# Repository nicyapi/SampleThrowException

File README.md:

<<<<<<< Updated upstream
<<<<<<< Updated upstream
# Lighthouse CI
=======
# Senior-Design-Project-maste
 
>>>>>>> Stashed changes
=======
# Senior-Design-Project-maste
 
>>>>>>> Stashed changes

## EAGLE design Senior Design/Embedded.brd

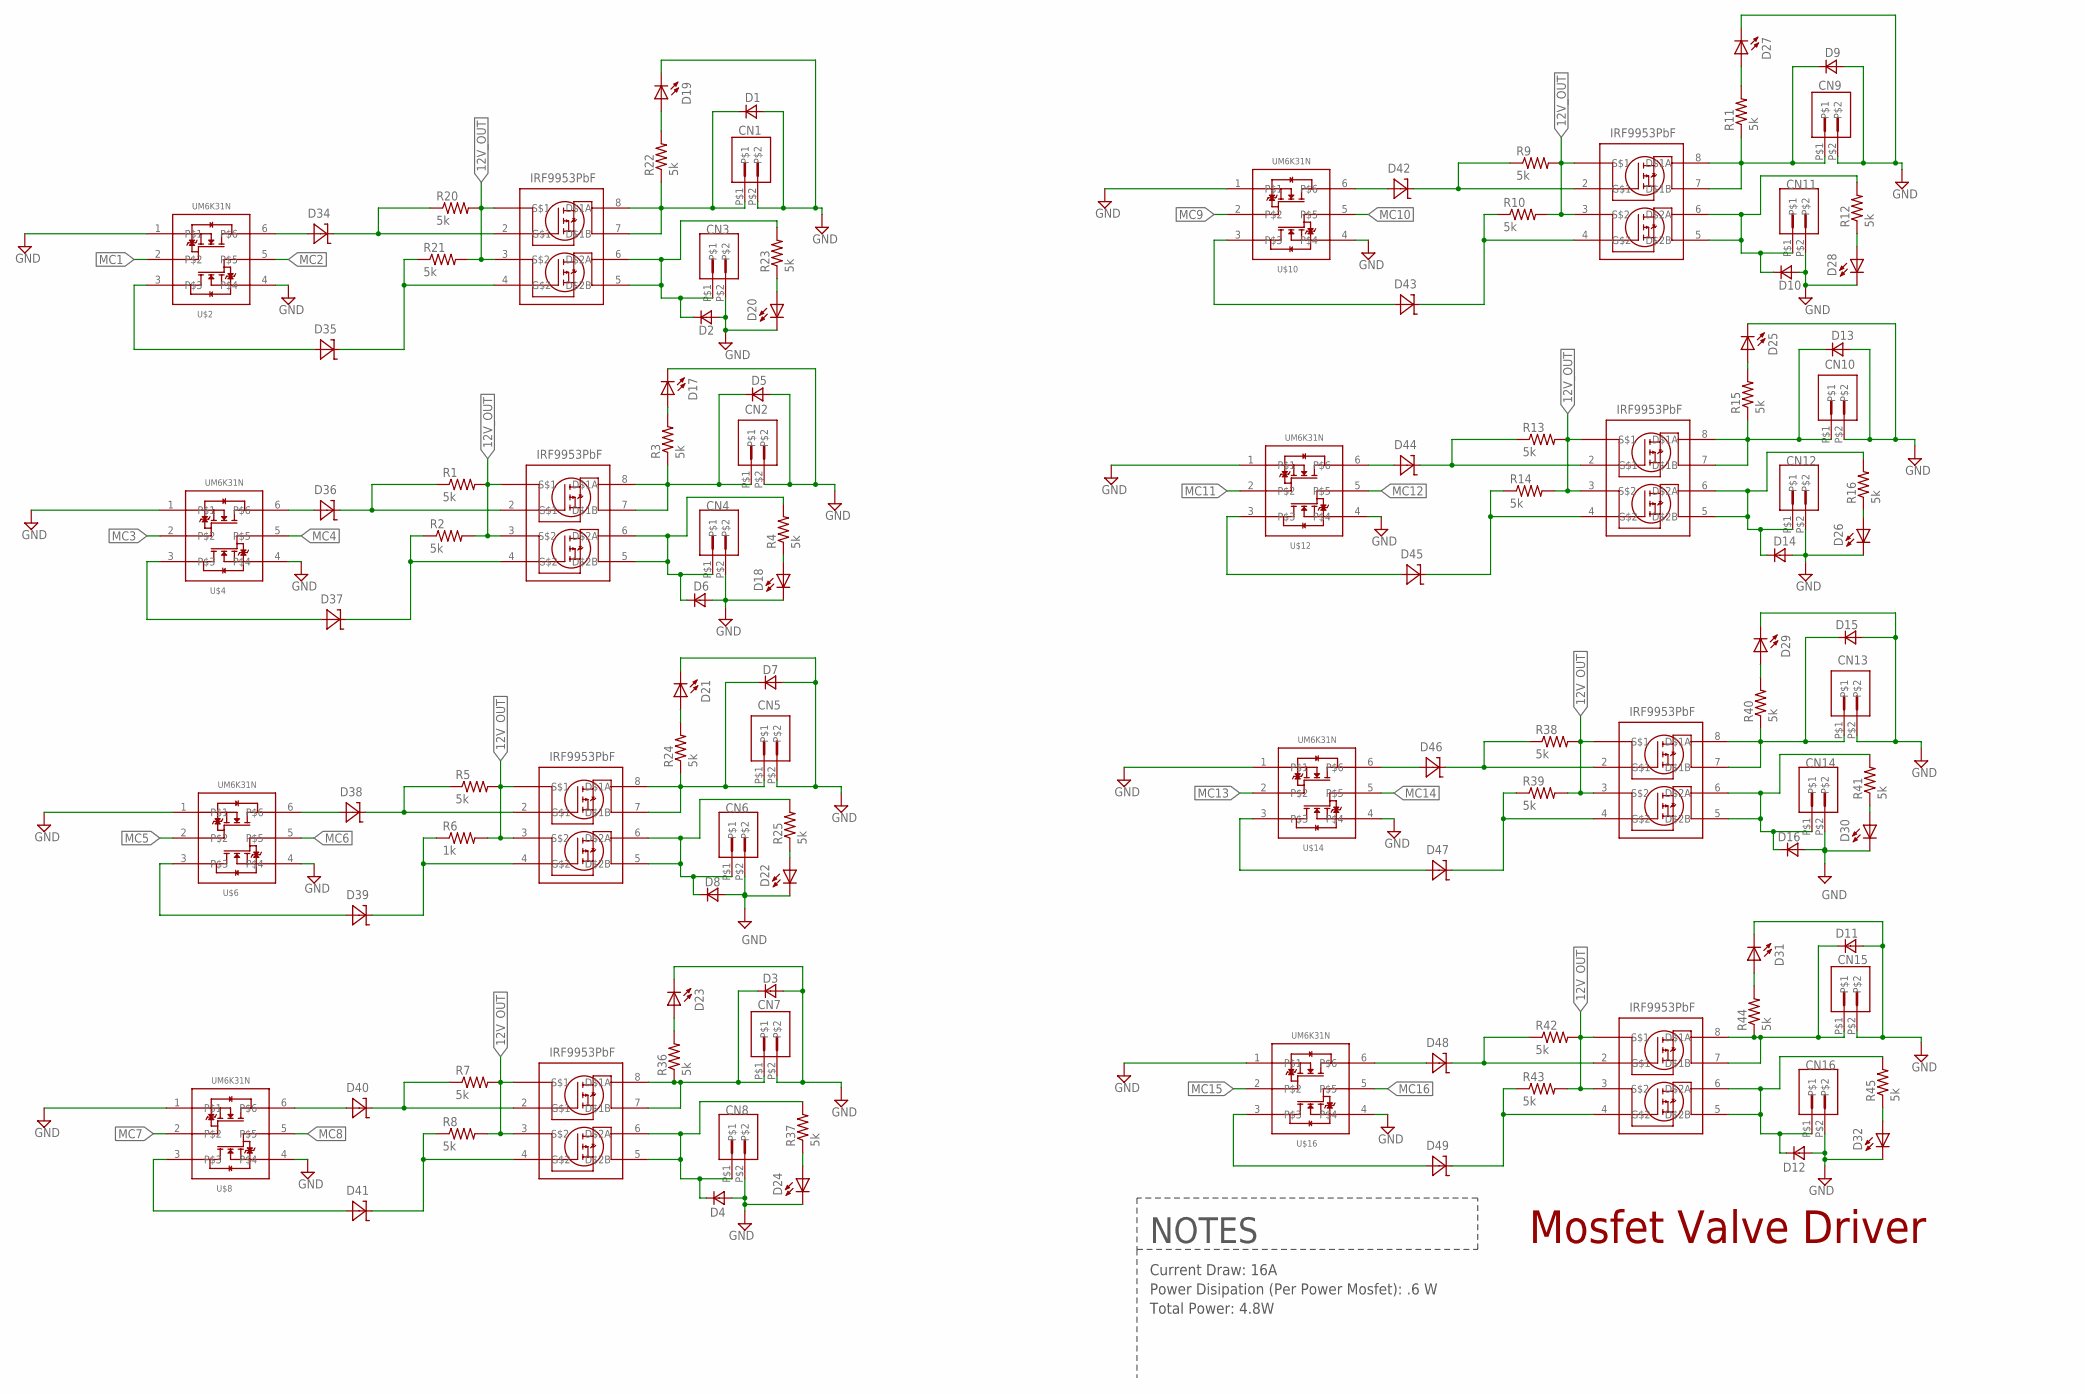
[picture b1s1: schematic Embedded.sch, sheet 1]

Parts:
CN1, CN2, CN3, CN4, CN5, CN6, CN7, CN8, CN9, CN10, CN11, CN12, CN13, CN14, CN15, CN16: KF2510-2; KF2540-2
D1, D2, D3, D4, D5, D6, D7, D8, D9, D10, D11, D12, D13, D14, D15, D16: RS1AL_DIODE; DO219
D17, D18, D19, D20, D21, D22, D23, D24, D25, D26, D27, D28, D29, D30, D31, D32: 1206LED; 1206
D34, D35, D37, D38, D39, D40, D41, D42, D43, D44, D45, D46, D47, D48, D49: 6.2V; SOD_323F
D36: 6.2; SOD_323F
R1, R2, R3, R4, R5, R7, R8, R9, R10, R11, R12, R13, R14, R15, R16, R20, R21, R22, R23, R24, R25, R36, R37, R38, R39, R40, R41, R42, R43, R44, R45: 5k; M0805
R6: 1k; M0805
U$1, U$3, U$5, U$7, U$9, U$11, U$13, U$15: IRF9953PBF; SO-8
U$2, U$4, U$6, U$8, U$10, U$12, U$14, U$16: UM6K31N; UMT6

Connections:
12V_OUT: R1.2, R2.2, R5.2, R6.2, R7.2, R8.2, R9.2, R10.2, R13.2, R14.2, R20.2, R21.2, R38.2, R39.2, R42.2, R43.2, U$1.1, U$1.3, U$3.1, U$3.3, U$5.1, U$5.3, U$7.1, U$7.3, U$9.1, U$9.3, U$11.1, U$11.3, U$13.1, U$13.3, U$15.1, U$15.3; also elsewhere on the board
GND: CN1.P$2, CN2.P$2, CN3.P$2, CN4.P$2, CN5.P$2, CN6.P$2, CN7.P$2, CN8.P$2, CN9.P$2, CN10.P$2, CN11.P$2, CN12.P$2, CN13.P$2, CN14.P$2, CN15.P$2, CN16.P$2, D1.A$2 (A), D2.A$2 (A), D3.A$2 (A), D4.A$2 (A), D5.A$2 (A), D6.A$2 (A), D7.A$2 (A), D8.A$2 (A), D9.A$2 (A), D10.A$2 (A), D11.A$2 (A), D12.A$2 (A), D13.A$2 (A), D14.A$2 (A), D15.A$2 (A), D16.A$2 (A), D17.P$2 (C), D18.P$2 (C), D19.P$2 (C), D20.P$2 (C), D21.P$2 (C), D22.P$2 (C), D23.P$2 (C), D24.P$2 (C), D25.P$2 (C), D26.P$2 (C), D27.P$2 (C), D28.P$2 (C), D29.P$2 (C), D30.P$2 (C), D31.P$2 (C), D32.P$2 (C), U$2.1, U$2.4, U$4.1, U$4.4, U$6.1, U$6.4, U$8.1, U$8.4, U$10.1, U$10.4, U$12.1, U$12.4, U$14.1, U$14.4, U$16.1, U$16.4; also elsewhere on the board
MC1: U$2.2; also elsewhere on the board
MC2: U$2.5; also elsewhere on the board
MC3: U$4.2; also elsewhere on the board
MC4: U$4.5; also elsewhere on the board
MC5: U$6.2; also elsewhere on the board
MC6: U$6.5; also elsewhere on the board
MC7: U$8.2; also elsewhere on the board
MC8: U$8.5; also elsewhere on the board
MC9: U$10.2; also elsewhere on the board
MC10: U$10.5; also elsewhere on the board
MC11: U$12.2; also elsewhere on the board
MC12: U$12.5; also elsewhere on the board
MC13: U$14.2; also elsewhere on the board
MC14: U$14.5; also elsewhere on the board
MC15: U$16.2; also elsewhere on the board
MC16: U$16.5; also elsewhere on the board
unnamed: D35.C, R21.1, U$1.4
unnamed: D35.A, U$2.3
unnamed: D37.C, R2.1, U$3.4
unnamed: D39.A, U$6.3
unnamed: D39.C, R6.1, U$5.4
unnamed: D40.A, U$8.6
unnamed: D41.C, R8.1, U$7.4
unnamed: D43.C, R10.1, U$9.4
unnamed: D45.C, R14.1, U$11.4
unnamed: D47.C, R39.1, U$13.4
unnamed: D49.C, R43.1, U$15.4
unnamed: D44.C, R13.1, U$11.2
unnamed: D45.A, U$12.3
unnamed: D43.A, U$10.3
unnamed: D42.C, R9.1, U$9.2
unnamed: D36.C, R1.1, U$3.2
unnamed: D37.A, U$4.3
unnamed: D36.A, U$4.6
unnamed: D34.C, R20.1, U$1.2
unnamed: D34.A, U$2.6
unnamed: D47.A, U$14.3
unnamed: D46.C, R38.1, U$13.2
unnamed: D49.A, U$16.3
unnamed: D48.C, R42.1, U$15.2
unnamed: D42.A, U$10.6
unnamed: D27.P$1 (A), R11.2
unnamed: D38.A, U$6.6
unnamed: D38.C, R5.1, U$5.2
unnamed: D40.C, R7.1, U$7.2
unnamed: D41.A, U$8.3
unnamed: D28.P$1 (A), R12.1
unnamed: D44.A, U$12.6
unnamed: D19.P$1 (A), R22.2
unnamed: D20.P$1 (A), R23.1
unnamed: D17.P$1 (A), R3.2
unnamed: D18.P$1 (A), R4.1
unnamed: D22.P$1 (A), R25.1
unnamed: D21.P$1 (A), R24.2
unnamed: D24.P$1 (A), R37.1
unnamed: D23.P$1 (A), R36.2
unnamed: D25.P$1 (A), R15.2
unnamed: D26.P$1 (A), R16.1
unnamed: D46.A, U$14.6
unnamed: D30.P$1 (A), R41.1
unnamed: D29.P$1 (A), R40.2
unnamed: D48.A, U$16.6
unnamed: D32.P$1 (A), R45.1
unnamed: D31.P$1 (A), R44.2
VAL_1: CN1.P$1, D1.C$1 (C), R22.1, U$1.7 (D$1B), U$1.8 (D$1A)
VAL_2: CN3.P$1, D2.C$1 (C), R23.2, U$1.5 (D$2B), U$1.6 (D$2A)
VAL_3: CN2.P$1, D5.C$1 (C), R3.1, U$3.7 (D$1B), U$3.8 (D$1A)
VAL_4: CN4.P$1, D6.C$1 (C), R4.2, U$3.5 (D$2B), U$3.6 (D$2A)
VAL_5: CN5.P$1, D7.C$1 (C), R24.1, U$5.7 (D$1B), U$5.8 (D$1A)
VAL_6: CN6.P$1, D8.C$1 (C), R25.2, U$5.5 (D$2B), U$5.6 (D$2A)
VAL_7: CN7.P$1, D3.C$1 (C), R36.1, U$7.7 (D$1B), U$7.8 (D$1A)
VAL_8: CN8.P$1, D4.C$1 (C), R37.2, U$7.5 (D$2B), U$7.6 (D$2A)
VAL_9: CN9.P$1, D9.C$1 (C), R11.1, U$9.7 (D$1B), U$9.8 (D$1A)
VAL_10: CN11.P$1, D10.C$1 (C), R12.2, U$9.5 (D$2B), U$9.6 (D$2A)
VAL_11: CN10.P$1, D13.C$1 (C), R15.1, U$11.7 (D$1B), U$11.8 (D$1A)
VAL_12: CN12.P$1, D14.C$1 (C), R16.2, U$11.5 (D$2B), U$11.6 (D$2A)
VAL_13: CN13.P$1, D15.C$1 (C), R40.1, U$13.7 (D$1B), U$13.8 (D$1A)
VAL_14: CN14.P$1, D16.C$1 (C), R41.2, U$13.5 (D$2B), U$13.6 (D$2A)
VAL_15: CN15.P$1, D11.C$1 (C), R44.1, U$15.7 (D$1B), U$15.8 (D$1A)
VAL_16: CN16.P$1, D12.C$1 (C), R45.2, U$15.5 (D$2B), U$15.6 (D$2A)

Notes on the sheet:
Mosfet Valve Driver
Current Draw: 16A
Power Disipation (Per Power Mosfet): .6 W
Total Power: 4.8W
NOTES

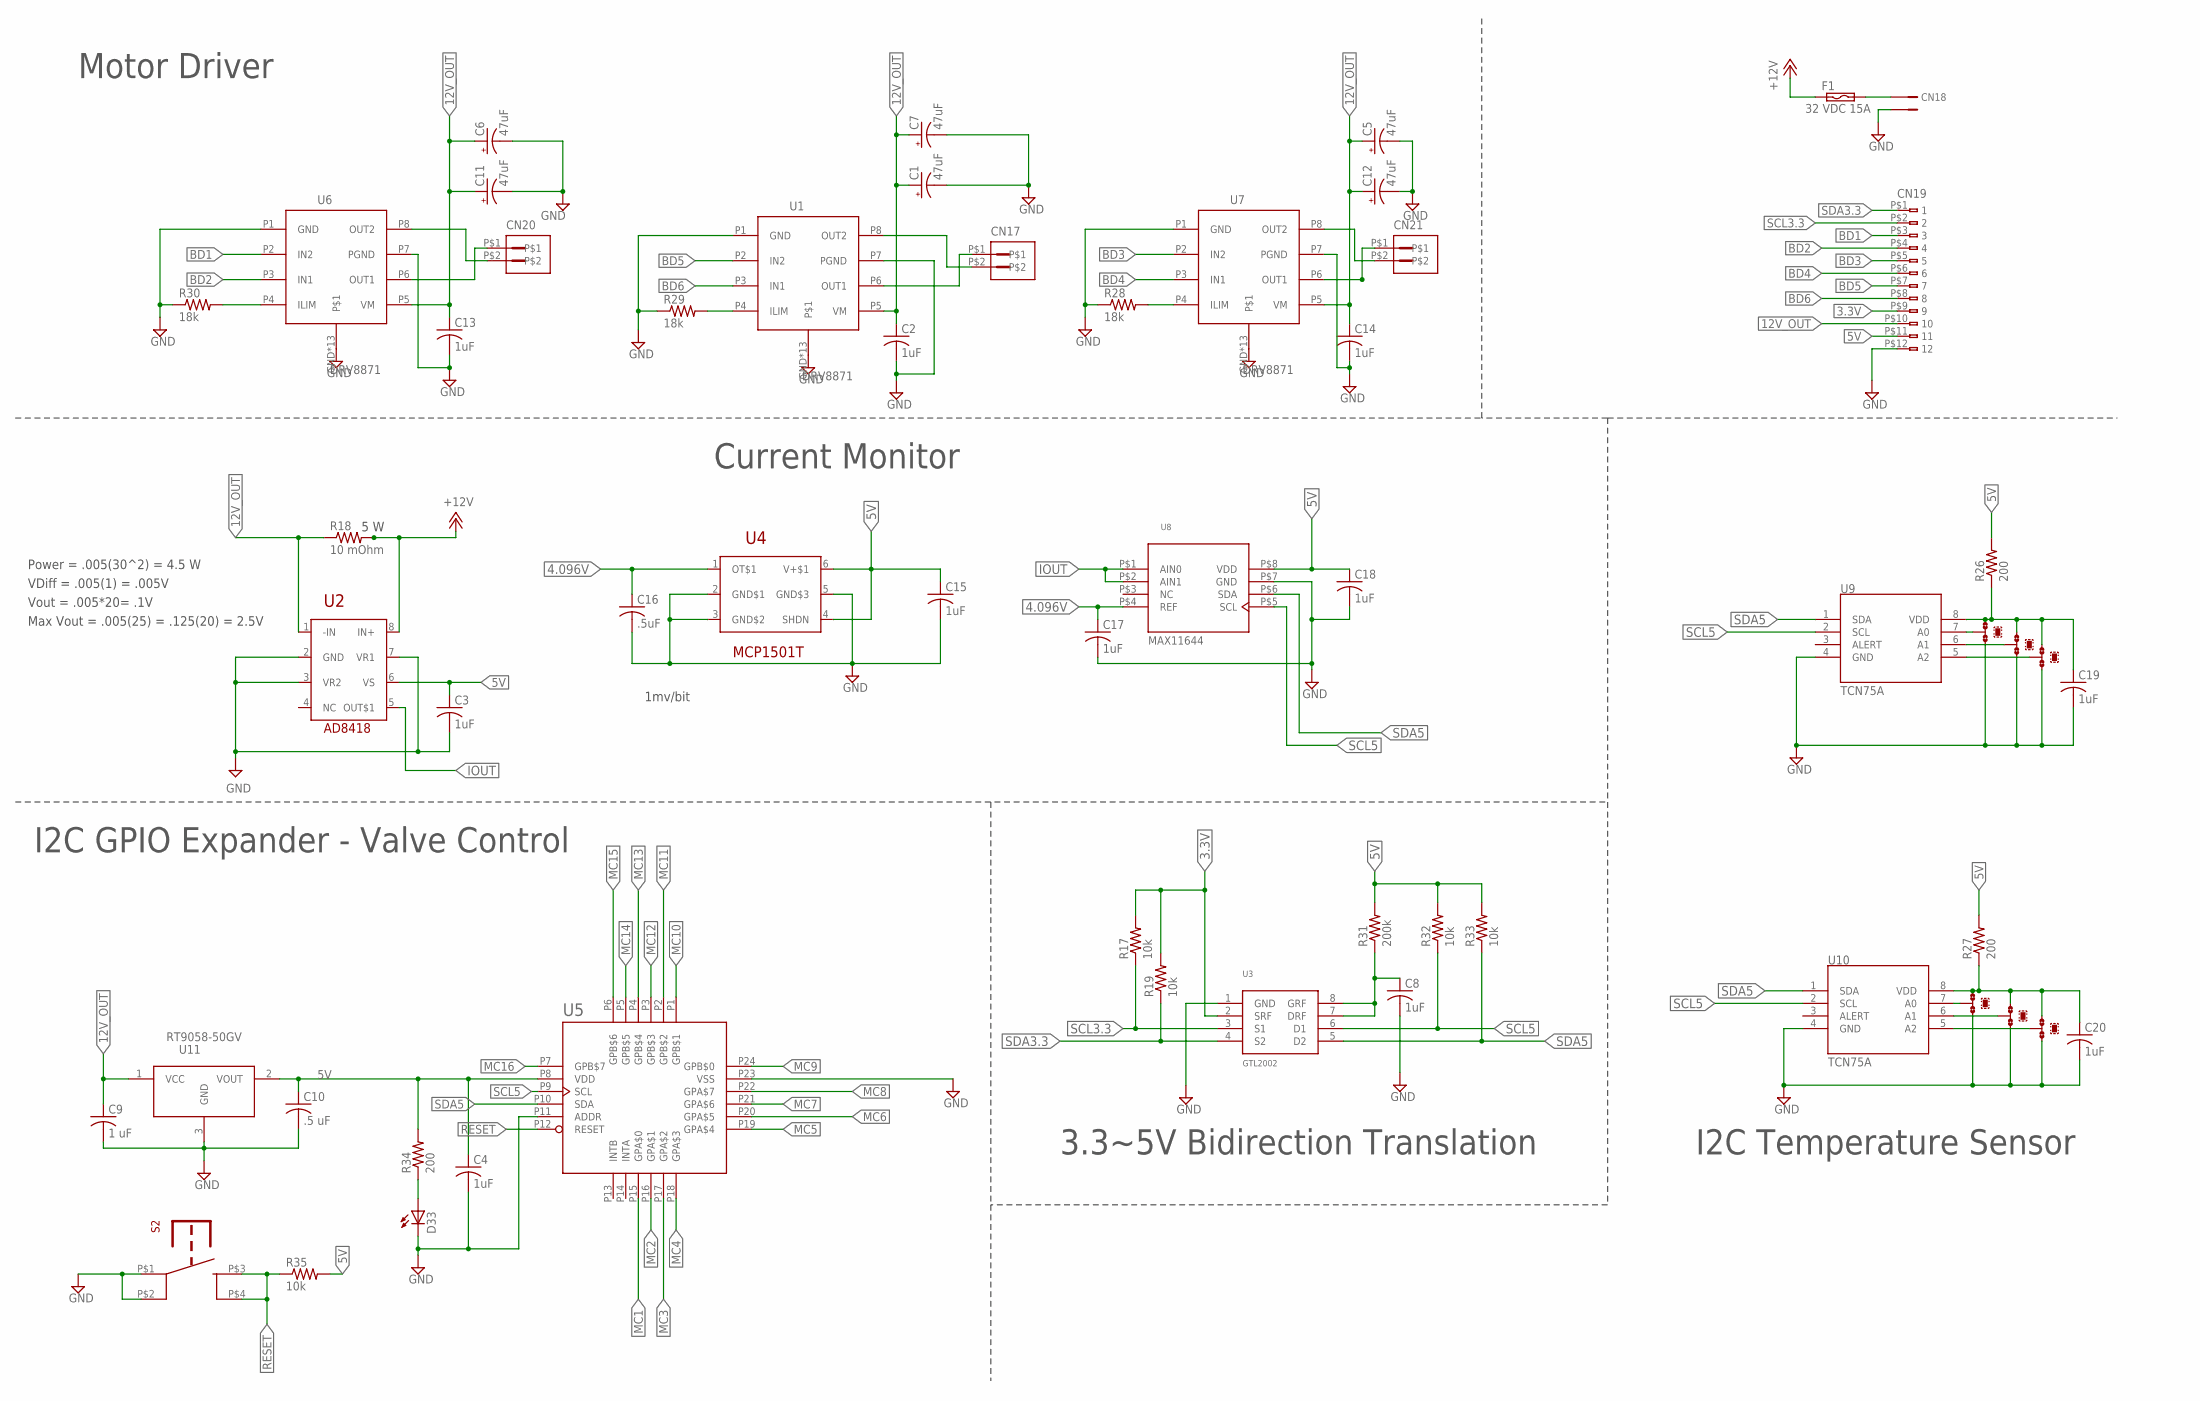
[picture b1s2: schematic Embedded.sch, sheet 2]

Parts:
C1, C5, C6, C7, C11, C12: 47uF; UD-6,3X7,7_NICHICON
C2, C3, C4, C8, C13, C14, C15, C17, C18, C19, C20: 1uF; C1206
C9: 1 uF; C1206
C10: .5 uF; C1206
C16: .5uF; C1206
CN17, CN20, CN21: KF2510-2; KF2540-2
CN18: PHEON_MKDS_CON; PHOEN_MKDS
CN19: MOLEX_FPC_52892_1233; MOLEX_WM1108
D33: 1206LED; 1206
F1: 32 VDC 15A; LITTLEFUSE125_003
JMP1, JMP2, JMP3, JMP4, JMP5, JMP6: 0R-JUMPA; A0R-JMP
R17, R19, R32, R33, R35: 10k; M0805
R18: 10 mOhm; 2818
R26, R27, R34: 200; M0805
R28, R29, R30: 18k; M0805
R31: 200k; M0805
S2: TL3305
U1, U6, U7: DRV8871; SO8_EP
U2: AD8418BZR; DGK_S-PDSO-G8
U3: GTL2002; SO-8
U4: MCP1501T-40E/CHY; SOT23-6
U5: MCP23018; QFN_24_EP
U8: MAX11645UMAX8; UMAX8
U9, U10: TCN75A; DGK_S-PDSO-G8
U11: RT9058-50GV; SOT23

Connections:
3.3V: CN19.P$9 (9), R17.2, R19.2, U3.2 (SRF)
4.096V: C16.1, C17.1, U4.1 (OT$1), U8.P$4 (REF)
5V: C3.1, C4.1, C10.1, C15.1, C18.1, CN19.P$11 (11), R26.2, R27.2, R31.2, R32.2, R33.2, R34.2, R35.2, U2.6 (VS), U4.4 (SHDN), U4.6 (V+$1), U5.P8 (VDD), U8.P$8 (VDD), U11.2 (VOUT)
12V_OUT: C1.+, C2.1, C5.+, C6.+, C7.+, C9.1, C11.+, C12.+, C13.1, C14.1, CN19.P$10 (10), R18.P$1 (1), U1.P5 (VM), U2.1 (-IN), U6.P5 (VM), U7.P5 (VM), U11.1 (VCC); also elsewhere on the board
+12V: F1.P$1 (1), R18.P$2 (2), U2.8 (IN+)
BD1: CN19.P$3 (3), U6.P2 (IN2)
BD2: CN19.P$4 (4), U6.P3 (IN1)
BD3: CN19.P$5 (5), U7.P2 (IN2)
BD4: CN19.P$6 (6), U7.P3 (IN1)
BD5: CN19.P$7 (7), U1.P2 (IN2)
BD6: CN19.P$8 (8), U1.P3 (IN1)
GND: C1.-, C2.2, C3.2, C4.2, C5.-, C6.-, C7.-, C8.2, C9.2, C10.2, C11.-, C12.-, C13.2, C14.2, C15.2, C16.2, C17.2, C18.2, C19.2, C20.2, CN18.P$2 (2), CN19.P$12 (12), D33.P$2 (C), JMP1.1, JMP2.1, JMP3.1, JMP4.1, JMP5.1, JMP6.1, R28.1, R29.1, R30.1, S2.P$1, S2.P$2, U1.GND, U1.P1 (GND), U1.P7 (PGND), U1.P$1, U1.P$2, U1.P$3, U1.P$4, U1.P$5, U1.P$6, U1.P$7, U1.P$8, U1.P$9, U1.P$10, U1.P$11, U1.P$12, U2.2 (GND), U2.3 (VR2), U2.7 (VR1), U3.1 (GND), U4.2 (GND$1), U4.3 (GND$2), U4.5 (GND$3), U5.P11 (ADDR), U5.P23 (VSS), U6.GND, U6.P1 (GND), U6.P7 (PGND), U6.P$1, U6.P$2, U6.P$3, U6.P$4, U6.P$5, U6.P$6, U6.P$7, U6.P$8, U6.P$9, U6.P$10, U6.P$11, U6.P$12, U7.GND, U7.P1 (GND), U7.P7 (PGND), U7.P$1, U7.P$2, U7.P$3, U7.P$4, U7.P$5, U7.P$6, U7.P$7, U7.P$8, U7.P$9, U7.P$10, U7.P$11, U7.P$12, U8.P$7 (GND), U9.4 (GND), U10.4 (GND), U11.3 (GND); also elsewhere on the board
IOUT: U2.5 (OUT$1), U8.P$1 (AIN0), U8.P$2 (AIN1)
KLJL: C8.1, R31.1, U3.7 (DRF), U3.8 (GRF)
MC1: U5.P15 (GPA$0); also elsewhere on the board
MC2: U5.P16 (GPA$1); also elsewhere on the board
MC3: U5.P17 (GPA$2); also elsewhere on the board
MC4: U5.P18 (GPA$3); also elsewhere on the board
MC5: U5.P19 (GPA$4); also elsewhere on the board
MC6: U5.P20 (GPA$5); also elsewhere on the board
MC7: U5.P21 (GPA$6); also elsewhere on the board
MC8: U5.P22 (GPA$7); also elsewhere on the board
MC9: U5.P24 (GPB$0); also elsewhere on the board
MC10: U5.P1 (GPB$1); also elsewhere on the board
MC11: U5.P2 (GPB$2); also elsewhere on the board
MC12: U5.P3 (GPB$3); also elsewhere on the board
MC13: U5.P4 (GPB$4); also elsewhere on the board
MC14: U5.P5 (GPB$5); also elsewhere on the board
MC15: U5.P6 (GPB$6); also elsewhere on the board
MC16: U5.P7 (GPB$7); also elsewhere on the board
unnamed: R29.2, U1.P4 (ILIM)
unnamed: CN17.P$2, U1.P8 (OUT2)
unnamed: D33.P$1 (A), R34.1
unnamed: CN17.P$1, U1.P6 (OUT1)
unnamed: JMP1.2, U9.7 (A0)
unnamed: JMP2.2, U9.6 (A1)
unnamed: JMP3.2, U9.5 (A2)
unnamed: JMP4.2, U10.7 (A0)
unnamed: JMP5.2, U10.6 (A1)
unnamed: R30.2, U6.P4 (ILIM)
unnamed: R28.2, U7.P4 (ILIM)
unnamed: CN20.P$2, U6.P8 (OUT2)
unnamed: CN20.P$1, U6.P6 (OUT1)
unnamed: CN21.P$1, U7.P6 (OUT1)
unnamed: CN21.P$2, U7.P8 (OUT2)
unnamed: JMP6.2, U10.5 (A2)
unnamed: CN18.P$1 (1), F1.P$2 (2)
ONKL: C20.1, JMP4.3, JMP5.3, JMP6.3, R27.1, U10.8 (VDD)
RESET: R35.1, S2.P$3, S2.P$4, U5.P12 (RESET)
SCL3.3: CN19.P$2 (2), R17.1, U3.3 (S1)
SCL5: R32.1, U3.6 (D1), U5.P9 (SCL), U8.P$5 (SCL), U9.2 (SCL), U10.2 (SCL)
SDA3.3: CN19.P$1 (1), R19.1, U3.4 (S2)
SDA5: R33.1, U3.5 (D2), U5.P10 (SDA), U8.P$6 (SDA), U9.1 (SDA), U10.1 (SDA)
UOY: C19.1, JMP1.3, JMP2.3, JMP3.3, R26.1, U9.8 (VDD)

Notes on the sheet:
Motor Driver
Current Monitor
I2C GPIO Expander - Valve Control
3.3~5V Bidirection Translation
VDiff = .005(1) = .005V
Vout = .005*20= .1V
Max Vout = .005(25) = .125(20) = 2.5V
Power = .005(30^2) = 4.5 W
5 W
1mv/bit
I2C Temperature Sensor

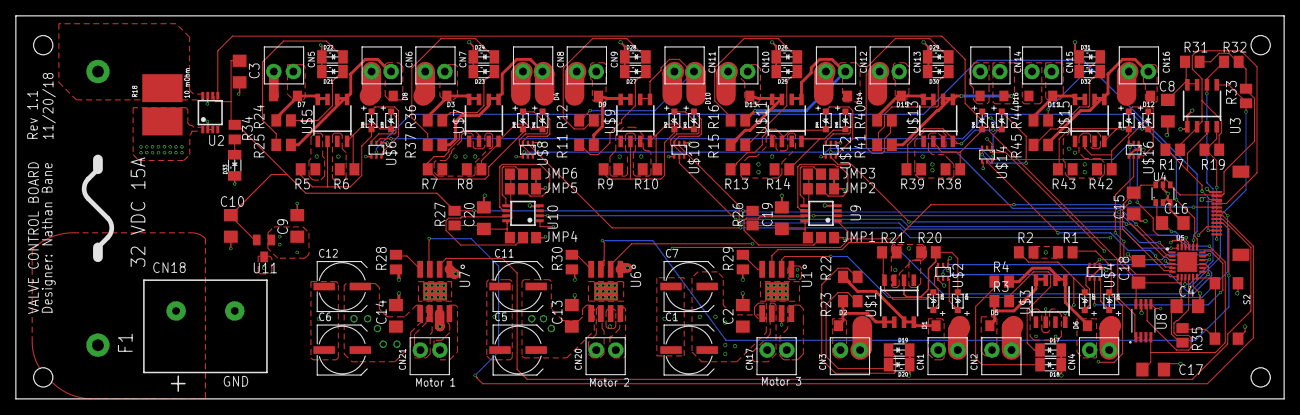
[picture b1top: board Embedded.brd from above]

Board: 4 copper layers, 164.8 x 49.8 mm, 170 parts (0 on the bottom side), 118 nets.

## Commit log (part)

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2021-10-06 git rebase --root
2021-10-14 git add -A|git restore -S -W -p&&git rebase --all
    This reverts commit 5fb7d89963b801a32abcd9350188b220eb714f05.
2021-10-14 index on C: c0b850b git add -A|git restore -S -W -p&&git rebase --all
2021-10-14 feat: add basic server command
2021-10-14 feat: add project CRUD routes
2021-10-14 feat: add loglevel and clean server exit
2021-10-14 feat: add project tokens
2021-10-14 fix: require token in collect
2021-10-14 refactor: move routes under api/ folder
2021-10-14 feat: save LHRs to server
2021-10-14 feat: add assert command
2021-10-14 refactor: split collect/report
2021-10-14 feat: add assertion preset support
2021-10-14 feat: add more collect launch flags
2021-10-14 tests: add script to test LH report
2021-10-14 fix: shorten auditUrl option name
    BREAKING CHANGE: auditUrl -> url
2021-10-14 tests: prepare tests for travis runs
2021-10-14 docs: update README with initial implementation
2021-10-14 chore: enable travis builds (#1)
2021-10-14 tests: update test expectations for separate repo
2021-10-14 chore: add required dependencies
2021-10-14 tests: typecheck in separate repo
2021-10-14 feat: add wizard for creating new project
2021-10-14 chore(ci): remove node 8 support to match lighthouse-core
2021-10-14 feat: upgrade to lighthouse 5.1.0
2021-10-14 chore: update jest to latest
2021-10-14 feat: native performance budget support
2021-10-14 chore: update lighthouse dependency to master
2021-10-14 feat: add max numeric value assertions
2021-10-14 fix: fail in pessimistic on partial audit failure
2021-10-14 feat: add url to run table
2021-10-14 tests: match bracing style
2021-10-14 feat: add multiple-url assertion support
2021-10-14 fix: file-relative path for rc-file extension
2021-10-14 feat: basic UI preact+parcel boilerplate
2021-10-14 tests: typecheck and lint jsx
2021-10-14 chore: add source map explorer script
2021-10-14 feat: serve UI from CLI server
2021-10-14 feat: lazy loaded routes
2021-10-14 tests: add very simple puppeteer UI test
2021-10-14 refactor: extract API loading to async-loader component
2021-10-14 chore: add license headers
2021-10-14 chore: add seed database scripts
2021-10-14 chore: remove use strict from modules
2021-10-14 feat: render clickable list of projects
2021-10-14 refactor: use ApiClient in hooks
2021-10-14 feat: add project fetch by id to API
2021-10-14 chore: mock fetch of api client
2021-10-14 feat: support build filtering by branch
2021-10-14 feat: add branch to build schema
2021-10-14 fix: convert externalBuildId to externalBuildUrl
    closes #6
2021-10-14 chore: update to tsc 3.5.3
2021-10-14 feat: add project dashboard shell
2021-10-14 feat: add findBuildById
2021-10-14 fix: allow project 404s
2021-10-14 feat: add statistic model
2021-10-14 fix: do not create duplicate statistic records
2021-10-14 fix: handle project 404s in UI
2021-10-14 perf: do not recompute statistics if all present
2021-10-14 feat: add project-wide urls route
2021-10-14 feat: add list branches endpoint
2021-10-14 feat: initial dashboard design
2021-10-14 fix: dashboard style tweaks
2021-10-14 feat: add basic plotly integration
2021-10-14 fix: sort stats by build time
2021-10-14 feat: add cursor tracking line
2021-10-14 feat: add category statistics
2021-10-14 feat: create real select dropdowns for header
2021-10-14 feat: use real data in dashboard graphs
2021-10-14 chore: move plotly shim to commonjs
2021-10-14 feat: wire dashboard data to header controls
2021-10-14 tests: refactor for introduction of e2e tests
2021-10-14 fix: renderable seed data
2021-10-14 fix(dashboard): handle multiple URLs
2021-10-14 fix: deterministic creation order in seed-data
2021-10-14 tests: switch away from chrome://version
2021-10-14 tests: remove debugging __event
2021-10-14 tests: wait for dashboard to completely load
2021-10-14 tests: add puppeteer screenshot tests
2021-10-14 tests: stricter table definition types
2021-10-14 feat: add context properties to build model
2021-10-14 tests: more forgiving in travis
2021-10-14 misc: update seed data with build context
2021-10-14 feat: add basic build view route
2021-10-14 test: add debug mode to e2e tests
2021-10-14 test: exercise client functionality in server tests
2021-10-14 feat: expose build sealing over API
2021-10-14 tests: better failure mode for wizard cli test
2021-10-14 feat: add representative and url filters to getRuns
2021-10-14 refactor: use correct preact fragment
2021-10-14 feat: add build score comparison to build view
2021-10-14 refactor(ui): use CSS variables for all sizes
2021-10-14 tests: add build url view tests
2021-10-14 feat: add build selector pill
2021-10-14 feat: add run data to build view
2021-10-14 feat: implement redesigned header
2021-10-14 refactor: restructure layout to allow pages to inject into header
2021-10-14 tests: unnecessary test variables
2021-10-14 feat(ui): add basic audit group comparison to build view
2021-10-14 fix(ui): center build pill comparison in header
2021-10-14 fix: seal the build after reporting
2021-10-14 feat: add audit detail pane
2021-10-14 feat(ui): add legend to build view
2021-10-14 feat: generate seed details items
2021-10-14 feat: add determinstic random generator
2021-10-14 refactor: rename `report` command to `upload`
2021-10-14 refactor: split seed data into multiple files
2021-10-14 feat: deterministic seed data
2021-10-14 refactor: split package into cli and utils
2021-10-14 refactor: split server package out from cli
2021-10-14 chore: move build scripts down to child packages
2021-10-14 tests: use unambiguous typedef ref
2021-10-14 refactor: move ApiClient to utils
2021-10-14 chore: update seed data with details
2021-10-14 feat: add basic audit diff finder
2021-10-14 tests: add more audit diff detail tests
2021-10-14 fix: only surface score diff level changes
2021-10-14 feat: add numeric diff to build view
2021-10-14 feat: only show audits with diffs
    - use same ordering between detail pane and audit groups
    - order audits by diff severity
    - hide audits without diff
2021-10-14 feat: add build hash selector placeholder
2021-10-14 fix: audit numeric value improvements are negative
2021-10-14 feat: add hash selector build list UI
2021-10-14 chore: move package dependcies to prepare for publish
2021-10-14 chore: add npmignore files
2021-10-14 docs: update references to CLI command lhci
2021-10-14 tests: update snapshots
2021-10-14 chore: enable public scope npm publishes
2021-10-14 tests: add noop close method for consistency
2021-10-14 feat: add support for postgres storage method
2021-10-14 fix: write stderr of failed LH runs
2021-10-14 feat(cli): infer real avatar URL
2021-10-14 chore: add dogfooding script to travis
2021-10-14 fix: do not double print token
2021-10-14 chore: print chrome version in travis
2021-10-14 fix: handle long commit messages
2021-10-14 chore: update chrome to latest stable
2021-10-14 tests: add missing ancestor test builds
2021-10-14 fix(server): do not fail for invalid uuids
2021-10-14 fix(cli): defer to travis commit info when available
2021-10-14 fix(cli): use previous commit as ancestor for master commits
2021-10-14 fix(server): no duplicate builds in hash selector
2021-10-14 fix(server): allow selection of same base/compare build
2021-10-14 feat(server): convert header project name to link
2021-10-14 fix(server): styling for no base build selected
2021-10-14 feat(server): add lhr viewer link
2021-10-14 fix(server): minor build view styling tweaks
2021-10-14 tests: combine postgres and xvfb declaration
2021-10-14 fix(server): handle 0 numericValue
2021-10-14 tests: switch travis to xenial
2021-10-14 tests: support static files in jest tests
2021-10-14 refactor(server): move audit group code into folder
2021-10-14 fix(server): treat no base as no diffs available
2021-10-14 feat(cli): print build view URL on upload
2021-10-14 fix: use position fixed for hash selector pane
2021-10-14 refactor(server): move audit detail to own folder
2021-10-14 fix(utils): diff finder handles overallSavingsMs
2021-10-14 feat(server): add basic table details
2021-10-14 feat(server): basic table styling
2021-10-14 tests: more accurate LH details types
2021-10-14 feat(server): support simple details types in table
2021-10-14 feat(utils): add getDiffLabel utility
2021-10-14 fix(server): responsive-ish container
2021-10-14 feat(server): update design for diff preview
2021-10-14 refactor(server): prefer className to class
2021-10-14 fix(utils): support non-url keyed item diffs
2021-10-14 refactor(utils): move getRowLabel into utils
2021-10-14 feat(server): table details diffs
2021-10-14 feat(server): table cell regression coloring
2021-10-14 fix(server): unify table and preview item regression defn
2021-10-14 fix(server): adjust default font and icon size
2021-10-14 feat(server): update gauge design
2021-10-14 refactor(server): extract project graphs to separate file
2021-10-14 feat(server): updated project dashboard design
2021-10-14 fix(server): update numeric diff preview design
2021-10-14 fix(server): use open triangle for fail
2021-10-14 tests(server): update e2e snapshots
2021-10-14 feat(cli): mask non-deterministic URL components
2021-10-14 tests(utils): add test for global regex replace
2021-10-14 feat(cli): additive collect mode
2021-10-14 tests: add multiple urls to our dogfood
2021-10-14 feat(utils): support other item generation
2021-10-14 tests(e2e): update snapshots for new data
2021-10-14 feat(server): support multiple URLs per graph
2021-10-14 fix(server): wire up build view URL dropdown
2021-10-14 tests(server): bump API fixtures
2021-10-14 feat(server): add legend for multiple URL dashboard graphs
2021-10-14 fix(server): only metrics get numeric diff view
2021-10-14 fix(server): audit details header design
2021-10-14 feat(server): show numeric diff in audit detail pane
2021-10-14 feat(utils): generate displayValue
2021-10-14 feat(server): use new ancestor logic in build view UI
2021-10-14 fix(server): do not use future biulds as ancestor on master
2021-10-14 fix(utils): update presets for inert audits
2021-10-14 refactor(utils): move representative run logic to utils
2021-10-14 feat(utils): add resource-summary sub property assertion support
2021-10-14 chore(cli): update lighthouse dependency to 5.5.0
2021-10-14 feat(utils): add median-run mergeMethod
2021-10-14 feat(cli): assert against budgets file
2021-10-14 feat(utils): convert budgets to assertions
2021-10-14 feat(server): use real sql migrations
2021-10-14 docs: more robust assertion documentation
2021-10-14 feat(server): use project tokens distinct from ids
2021-10-14 fix(cli): usability improvements to assert output
2021-10-14 fix(cli): handle Lighthouse failure
2021-10-14 feat(cli): add command to open HTML reports
2021-10-14 feat(cli): save assertion results to disk
2021-10-14 refactor(cli): rename mergeMethod -> aggregationMethod
2021-10-14 feat(utils): add support for default aggregationMethod
2021-10-14 feat(cli): add github status checks
2021-10-14 tests(cli): ensure token does not leak into upload tests
2021-10-14 fix(cli): improved debug output for status check
2021-10-14 tests(e2e): deflake image screenshots
2021-10-14 feat(server): use compareUrl from searchParams
2021-10-14 fix(cli): status check message improvements
2021-10-14 fix(server): use baseHash override
2021-10-14 docs: add getting started guide
2021-10-14 feat(utils): empty build in seed data
2021-10-14 feat(utils): find displayValue diffs
2021-10-14 fix(server): improved numeric diff unit inferrence
2021-10-14 feat(server): add display value audit diff
2021-10-14 fix(server): hide just displayValue diffs
2021-10-14 fix(server): handle invalid URLs
2021-10-14 feat(utils): ignore passing->passing numericValue only changes
2021-10-14 feat(utils): diff finder use non-url item keys
2021-10-14 fix(server): audit panel close button design
2021-10-14 Revert "Revert "Revert "Revert "Revert "Revert "Revert "Revert "$$""""""""
    This reverts commit 73ef3c6023d9df33af26d20aeb422f2aa0318dd7.
2021-10-14 Revert "Revert "Revert "Revert "Revert "Revert "Revert "Revert "Revert "$$"""""""""
    This reverts commit 1acbe118a2a6fb6d65731622d567dace0773b024.
